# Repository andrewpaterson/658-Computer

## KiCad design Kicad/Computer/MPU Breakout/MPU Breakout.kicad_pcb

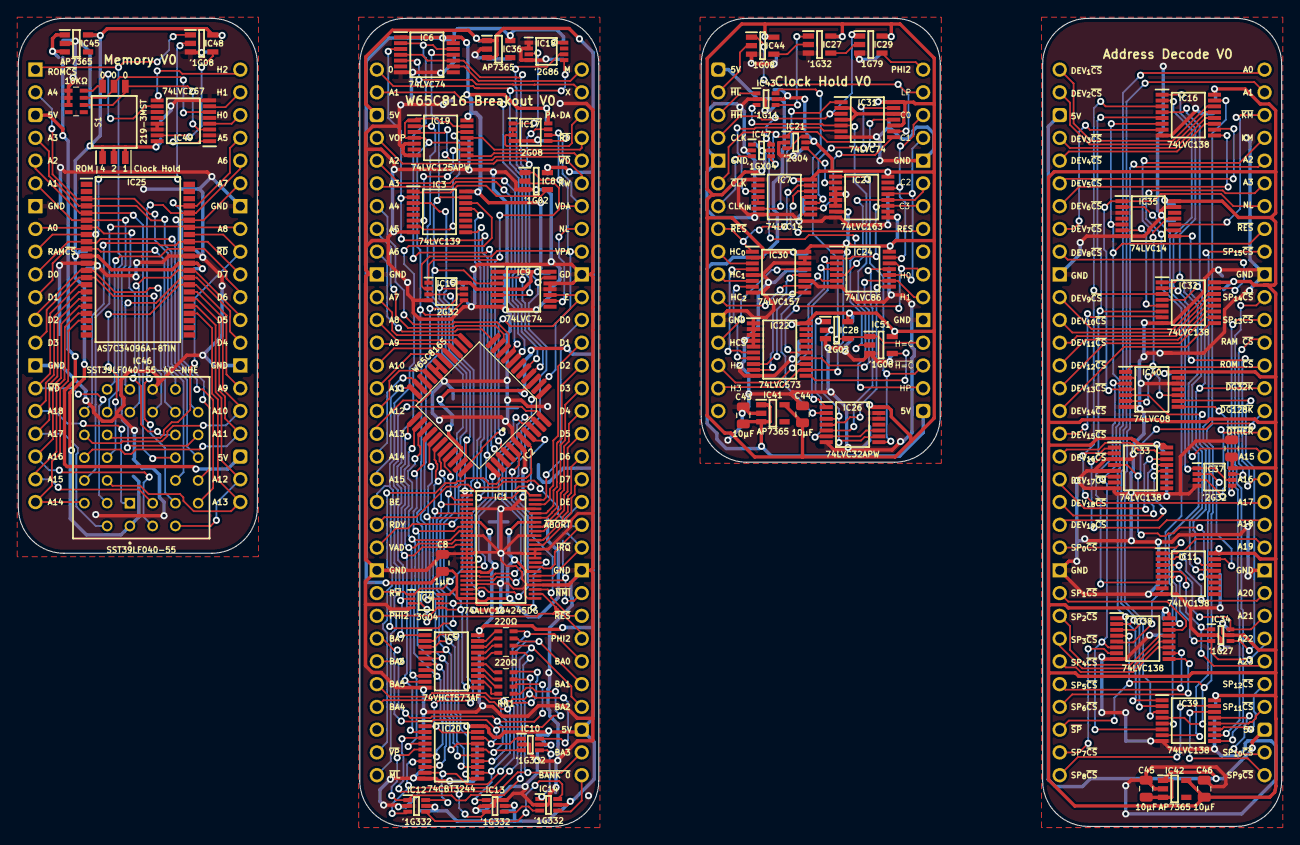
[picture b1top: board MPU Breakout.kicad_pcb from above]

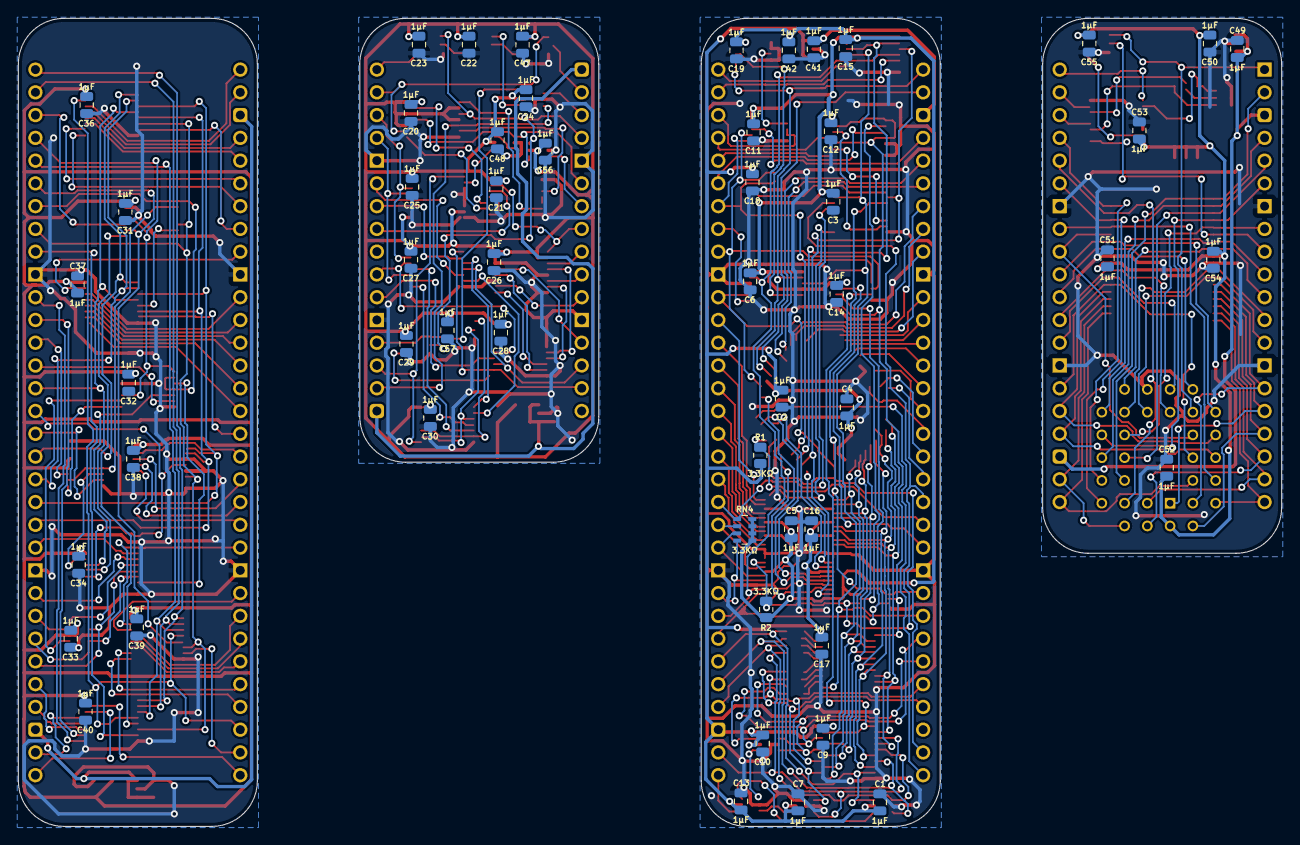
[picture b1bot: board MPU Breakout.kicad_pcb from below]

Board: 2 copper layers, 118 parts (54 on the bottom side), 254 nets.

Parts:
C1, C2, C3, C4, C5, C6, C7, C8, C9, C10, C11, C12, C13, C14, C15, C16, C17, C18, C19, C20, C21, C22, C23, C24, C25, C26, C27, C28, C29, C30, C31, C32, C33, C34, C35, C36, C37, C38, C39, C40, C41, C42, C47, C48, C49, C50, C51, C52, C53, C54, C55, C56, C57: 1μF; C_0805
C43, C44, C45, C46: 10μF; C_0805
IC1: 74ALVC164245DGG,11; SOP50P810X120-48N
IC2: W65C816S6TQG-14; W65C816 PLCC 0.8mm 44 Pin
IC3: 74LVC139PW,118; SOP65P640X110-16N
IC4: SN74LVC3G04DCUR; SOP50P310X90-8N
IC5: 74VHCT573AFT; SOP65P640X120-20N
IC6, IC9, IC31: 74LVC74APW,118; SOP65P640X110-14N
IC7, IC35: SN74LVC14APWRG4; SOP65P640X110-14N
IC8, IC28: 74LVC1G02GV,125; SOT95P275X110-5N
IC10, IC12, IC13, IC14: SN74LVC1G332DCKRG4; SOT65P210X110-6N
IC11, IC16, IC32, IC33, IC38, IC39: 74LVC138APW-Q100J; SOP65P640X110-16N
IC15, IC37: 74LVC2G32DP,125; SOP65P400X110-8N
IC17: 74LVC2G08DP-Q100H; SOP65P400X110-8N
IC18: 74LVC2G86DP,125; SOP65P400X110-8N
IC19: 74LVC125APW-Q100J; SOP65P640X110-14N
IC20: SN74CBT3244CPWR; SOP65P640X120-20N
IC21: 74LVC2G04GW-Q100H; SOP65P210X110-6N
IC22: 74LVC573APW,118; SOP65P640X110-20N
IC23: 74LVC163PW,118; SOP65P640X110-16N
IC24: SN74LVC86APWR; SOP65P640X120-14N
IC25: AS7C34096A-8TIN; SOP80P1176X120-44N
IC26: 74LVC32APW,118; SOP65P640X110-14N
IC27: 74LVC1G32GV,125; SOT95P275X110-5N
IC29: 74LVC1G79GV,125; SOT95P275X110-5N
IC30: 74LVC157APW,118; SOP65P640X110-16N
IC34: 74LVC1G27GW,125; SOP65P210X110-6N
IC36, IC41, IC42, IC45: AP7365-33WG-7; SOT95P285X130-5N
IC40: 74LVC08APW,112; SOP65P640X110-14N
IC43: 74LVC1G11GW-Q100H; SOP65P210X110-6N
IC44, IC48, IC51: 74LVC1G08GV,125; SOT95P275X110-5N
IC46: SST39LF040-55-4C-NHE; 5408803224008
IC47: 74LVC1GX04GW,125; SOP65P210X110-6N
IC49: 74LVC257APW,118; SOP65P640X110-16N
J1: Conn_02x16_Counter_Clockwise; DIP-32_Board_W22.86mm
J2, J7: Conn_02x32_Counter_Clockwise; DIP-64_Board_W22.86mm
J8: Conn_02x20_Counter_Clockwise; DIP-40_Board_W22.86mm
R1, R2: 3.3KΩ; R_0805
RN1, RN2: CAY16-221J4LF; CAY1647R0F4LF
RN3: CAY16-103J4LF; CAY16-J4
RN4: CAY16-332J4LF; CAY16332J4LF
S1: 219-3MST; SOIC127P844X265-6N

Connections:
/Address Decode Board/3.3V: C31.1, C32.1, C33.1, C34.1, C35.1, C36.1, C37.1, C38.1, C39.1, C40.1, C46.1, IC11.16 (3V), IC16.16 (3V), IC32.16 (3V), IC33.16 (3V), IC34.5 (3V), IC35.14 (3V), IC37.8 (VCC), IC38.16 (3V), IC39.16 (3V), IC40.14 (3V), IC42.5 (VOUT)
/Address Decode Board/5V: C45.1, IC42.1 (VIN), IC42.3 (EN), J2.3, J2.35
/Address Decode Board/A0: IC38.1 (A0), IC39.1 (A0), J2.64
/Address Decode Board/A1: IC38.2 (A1), IC39.2 (A1), J2.63
/Address Decode Board/A2: IC38.3 (A2), IC39.3 (A2), J2.60
/Address Decode Board/A3: IC35.9 (4A), IC38.5 (~E2), J2.59
/Address Decode Board/A15: IC16.1 (A0), IC32.1 (A0), J2.47
/Address Decode Board/A16: IC16.2 (A1), IC32.2 (A1), J2.46
/Address Decode Board/A17: IC16.3 (A2), IC32.3 (A2), IC33.1 (A0), J2.45
/Address Decode Board/A18: IC16.5 (~E2), IC32.6 (E3), IC33.2 (A1), J2.44
/Address Decode Board/A19: IC11.1 (A0), J2.43
/Address Decode Board/A20: IC11.2 (A1), J2.41
/Address Decode Board/A21: IC11.3 (A2), IC34.6 (C), J2.40
/Address Decode Board/A22: IC11.5 (~E2), IC34.3 (B), J2.39
/Address Decode Board/A23: IC11.4 (~E1), IC34.1 (A), J2.38
/Address Decode Board/GND: C31.2, C32.2, C33.2, C34.2, C35.2, C36.2, C37.2, C38.2, C39.2, C40.2, C45.2, C46.2, IC11.8 (GND), IC16.8 (GND), IC32.8 (GND), IC33.3 (A2), IC33.5 (~E2), IC33.8 (GND), IC34.2 (GND), IC35.3 (2A), IC35.7 (GND), IC35.13 (6A), IC37.4 (GND), IC38.8 (GND), IC39.8 (GND), IC40.7 (GND), IC40.12 (4A), IC40.13 (4B), IC42.2 (GND), J2.10, J2.23, J2.42, J2.55
/Address Decode Board/Kernal Mode: IC35.11 (5A), IC40.1 (1A), IC40.10 (3B), J2.61
/Address Decode Board/Kernal Mode·Native Latch: IC11.6 (E3), IC40.3 (1Y)
/Address Decode Board/Native Latch: IC35.1 (1A), IC40.2 (1B), IC40.4 (2A), J2.58
/Address Decode Board/~A21+A22+A23: IC34.4 (Y), IC40.9 (3A)
/Address Decode Board/~Device Group 32K: IC11.13 (~Y2), IC16.4 (~E1), IC32.4 (~E1), J2.50
/Address Decode Board/~Device Group 128K: IC11.12 (~Y3), IC33.4 (~E1), J2.49
/Address Decode Board/~Device _{CS1}: IC16.14 (~Y1), J2.1
/Address Decode Board/~Device _{CS2}: IC16.13 (~Y2), J2.2
/Address Decode Board/~Device _{CS3}: IC16.12 (~Y3), J2.4
/Address Decode Board/~Device _{CS4}: IC16.11 (~Y4), J2.5
/Address Decode Board/~Device _{CS5}: IC16.10 (~Y5), J2.6
/Address Decode Board/~Device _{CS6}: IC16.9 (~Y6), J2.7
/Address Decode Board/~Device _{CS7}: IC16.7 (~Y7), J2.8
/Address Decode Board/~Device _{CS8}: IC32.15 (~Y0), J2.9
/Address Decode Board/~Device _{CS9}: IC32.14 (~Y1), J2.11
/Address Decode Board/~Device _{CS10}: IC32.13 (~Y2), J2.12
/Address Decode Board/~Device _{CS11}: IC32.12 (~Y3), J2.13
/Address Decode Board/~Device _{CS12}: IC32.11 (~Y4), J2.14
/Address Decode Board/~Device _{CS13}: IC32.10 (~Y5), J2.15
/Address Decode Board/~Device _{CS14}: IC32.9 (~Y6), J2.16
/Address Decode Board/~Device _{CS15}: IC32.7 (~Y7), J2.17
/Address Decode Board/~Device _{CS16}: IC33.15 (~Y0), J2.18
/Address Decode Board/~Device _{CS17}: IC33.14 (~Y1), J2.19
/Address Decode Board/~Device _{CS18}: IC33.13 (~Y2), J2.20
/Address Decode Board/~Device _{CS19}: IC33.12 (~Y3), J2.21
/Address Decode Board/~Kernal Mode: IC35.10 (5Y), J2.62
/Address Decode Board/~Native Latch: IC35.2 (1Y), IC37.1 (1A), IC37.6 (2B)
/Address Decode Board/~OTHER: IC37.3 (2Y), J2.48
/Address Decode Board/~RAM_{CS}: IC37.7 (1Y), J2.52
/Address Decode Board/~ROM_{CS}: IC40.6 (2Y), J2.51
/Address Decode Board/~Reset: IC16.6 (E3), IC33.6 (E3), IC35.5 (3A), IC38.6 (E3), IC39.6 (E3), J2.57
/Address Decode Board/~SPECIAL: IC16.15 (~Y0), IC38.4 (~E1), IC39.4 (~E1), J2.30
/Address Decode Board/~Special _{CS0}: IC38.15 (~Y0), J2.22
/Address Decode Board/~Special _{CS1}: IC38.14 (~Y1), J2.24
/Address Decode Board/~Special _{CS2}: IC38.13 (~Y2), J2.25
/Address Decode Board/~Special _{CS3}: IC38.12 (~Y3), J2.26
/Address Decode Board/~Special _{CS4}: IC38.11 (~Y4), J2.27
/Address Decode Board/~Special _{CS5}: IC38.10 (~Y5), J2.28
/Address Decode Board/~Special _{CS6}: IC38.9 (~Y6), J2.29
/Address Decode Board/~Special _{CS7}: IC38.7 (~Y7), J2.31
/Address Decode Board/~Special _{CS8}: IC39.15 (~Y0), J2.32
/Address Decode Board/~Special _{CS9}: IC39.14 (~Y1), J2.33
/Address Decode Board/~Special _{CS10}: IC39.13 (~Y2), J2.34
/Address Decode Board/~Special _{CS11}: IC39.12 (~Y3), J2.36
/Address Decode Board/~Special _{CS12}: IC39.11 (~Y4), J2.37
/Address Decode Board/~Special _{CS13}: IC39.10 (~Y5), J2.53
/Address Decode Board/~Special _{CS14}: IC39.9 (~Y6), J2.54
/Address Decode Board/~Special _{CS15}: IC39.7 (~Y7), J2.56
/Clock Control Board/3.3V: C20.1, C21.1, C22.1, C23.1, C24.1, C25.1, C26.1, C27.1, C28.1, C29.1, C30.1, C44.1, C47.1, C48.1, C56.1, C57.1, IC7.14 (3V), IC21.5 (3V), IC22.20 (3V), IC23.7 (CEP), IC23.9 (~PE), IC23.10 (CET), IC23.16 (3V), IC24.14 (3V), IC26.14 (3V), IC27.5 (3V), IC28.5 (3V), IC29.5 (3V), IC30.2 (1I0), IC30.16 (3V), IC31.2 (1D), IC31.4 (~1SD), IC31.10 (~2SD), IC31.12 (2D), IC31.14 (3V), IC41.5 (VOUT), IC43.5 (3V), IC44.5 (3V), IC47.5 (3V), IC51.5 (3V)
/Clock Control Board/5V: C43.1, IC41.1 (VIN), IC41.3 (EN), J1.1, J1.17
/Clock Control Board/CLK: IC29.1 (D), IC31.3 (1CP), IC47.6 (Y), IC51.2 (A), J1.4
/Clock Control Board/CLK H.P.: IC7.4 (2Y), IC7.5 (3A)
/Clock Control Board/CLK High Pulse: IC31.5 (1Q), IC43.3 (B), J1.18
/Clock Control Board/CLK L.P.: IC7.8 (4Y), IC7.11 (5A)
/Clock Control Board/CLK Low Pulse: IC31.9 (2Q), IC44.1 (B), J1.31
/Clock Control Board/CLK_{IN}: IC47.3 (X1), J1.7
/Clock Control Board/Clk Count_{0}: IC23.14 (Q0), IC24.13 (4B), J1.30
/Clock Control Board/Clk Count_{1}: IC23.13 (Q1), IC24.10 (3B), J1.29
/Clock Control Board/Clk Count_{2}: IC23.12 (Q2), IC24.5 (2B), J1.27
/Clock Control Board/Clk Count_{3}: IC23.11 (Q3), IC24.2 (1B), J1.26
/Clock Control Board/GND: C20.2, C21.2, C22.2, C23.2, C24.2, C25.2, C26.2, C27.2, C28.2, C29.2, C30.2, C43.2, C44.2, C47.2, C48.2, C56.2, C57.2, IC7.1 (1A), IC7.7 (GND), IC21.2 (GND), IC22.1 (~OE), IC22.2 (D0), IC22.3 (D1), IC22.4 (D2), IC22.5 (D3), IC22.10 (GND), IC23.3 (D0), IC23.4 (D1), IC23.5 (D2), IC23.6 (D3), IC23.8 (GND), IC24.7 (GND), IC26.7 (GND), IC26.12 (4A), IC26.13 (4B), IC27.3 (GND), IC28.3 (GND), IC29.3 (GND), IC30.5 (2I0), IC30.8 (GND), IC30.11 (3I0), IC30.14 (4I0), IC30.15 (~E), IC31.7 (GND), IC41.2 (GND), IC43.2 (GND), IC44.3 (GND), IC47.2 (GND), IC51.3 (GND), J1.5, J1.12, J1.21, J1.28
/Clock Control Board/HC Latch_{0}: IC22.15 (Q4), IC24.12 (4A), J1.23
/Clock Control Board/HC Latch_{1}: IC22.14 (Q5), IC24.9 (3A), J1.22
/Clock Control Board/HC Latch_{2}: IC22.13 (Q6), IC24.4 (2A), J1.14
/Clock Control Board/HC Latch_{3}: IC22.12 (Q7), IC24.1 (1A), J1.15
/Clock Control Board/HC=CC: IC28.4 (Y), IC43.6 (C), IC51.1 (B), J1.20
/Clock Control Board/High Pulse+Low Pulse: IC27.4 (Y), IC29.2 (CP)
/Clock Control Board/Hold Count_{0}: IC22.6 (D4), IC30.4 (1Y)
/Clock Control Board/Hold Count_{0}D: IC30.3 (1I1), J1.9
/Clock Control Board/Hold Count_{1}: IC22.7 (D5), IC30.7 (2Y)
/Clock Control Board/Hold Count_{1}D: IC30.6 (2I1), J1.10
/Clock Control Board/Hold Count_{2}: IC22.8 (D6), IC30.9 (3Y)
/Clock Control Board/Hold Count_{2}D: IC30.10 (3I1), J1.11
/Clock Control Board/Hold Count_{3}: IC22.9 (D7), IC30.12 (4Y)
/Clock Control Board/Hold Count_{3}D: IC30.13 (4I1), J1.13
/Clock Control Board/Latch CHC: IC22.11 (LE), IC51.4 (Y)
/Clock Control Board/PHI2: IC29.4 (Q), J1.32
/Clock Control Board/Reset: IC7.12 (6Y), J1.25
/Clock Control Board/~CLK High Pulse: IC7.3 (2A), IC31.6 (~1Q)
/Clock Control Board/~CLK High Reset Pulse: IC7.6 (3Y), IC31.1 (~1RD)
/Clock Control Board/~CLK Low Pulse: IC7.9 (4A), IC31.8 (~2Q)
/Clock Control Board/~CLK Low Reset Pulse: IC7.10 (5Y), IC31.13 (~2RD)
/Clock Control Board/~CLK: IC21.1 (1A), IC31.11 (2CP), IC47.4 (~Y), J1.6
/Clock Control Board/~CLK_{DRAGGED}: IC21.4 (2Y), IC23.2 (CP)
/Clock Control Board/~HC=CC: IC23.1 (~MR), IC26.8 (3Y), J1.19
/Clock Control Board/~HC_{0=CC_{0}}: IC24.11 (4Y), IC26.5 (2B)
/Clock Control Board/~HC_{1=CC_{1}}: IC24.8 (3Y), IC26.4 (2A)
/Clock Control Board/~HC_{2=CC_{2}}: IC24.6 (2Y), IC26.2 (1B)
/Clock Control Board/~HC_{3=CC_{3}}: IC24.3 (1Y), IC26.1 (1A)
/Clock Control Board/~HC_{H=CC_{H}}: IC26.3 (1Y), IC26.9 (3A), IC28.2 (A)
/Clock Control Board/~HC_{L=CC_{L}}: IC26.6 (2Y), IC26.10 (3B), IC28.1 (B)
/Clock Control Board/~Hold High: IC43.1 (A), J1.3
/Clock Control Board/~Hold High·CLK High Pulse·HC=CC: IC27.1 (B), IC43.4 (Y)
/Clock Control Board/~Hold Low: IC44.2 (A), J1.2
/Clock Control Board/~Hold Low·CLK Low Pulse: IC27.2 (A), IC44.4 (Y)
/Clock Control Board/~Reset: IC7.13 (6A), IC30.1 (S), J1.8
/Memory Board/3.3V: C50.1, C51.1, C52.1, C53.1, C54.1, C55.1, IC25.11 (3V), IC25.33 (3V), IC45.5 (VOUT), IC46.32 (3V), IC48.5 (3V), IC49.16 (3V), S1.1, S1.2, S1.3
/Memory Board/5V: C49.1, IC45.1 (VIN), IC45.3 (EN), J8.3, J8.23
/Memory Board/A0: IC25.7 (A0), IC46.12 (A0), J8.8
/Memory Board/A1: IC25.6 (A1), IC46.11 (A1), J8.6
/Memory Board/A2: IC25.5 (A2), IC46.10 (A2), J8.5
/Memory Board/A3: IC25.4 (A3), IC46.9 (A3), J8.4
/Memory Board/A4: IC25.3 (A4), IC46.8 (A4), J8.2
/Memory Board/A5: IC25.41 (A5), IC46.7 (A5), J8.37
/Memory Board/A6: IC25.40 (A6), IC46.6 (A6), J8.36
/Memory Board/A7: IC25.39 (A7), IC46.5 (A7), J8.35
/Memory Board/A8: IC25.38 (A8), IC46.27 (A8), J8.33
/Memory Board/A9: IC25.30 (A9), IC46.26 (A9), J8.26
/Memory Board/A10: IC25.29 (A10), IC46.23 (A10), J8.25
/Memory Board/A11: IC25.28 (A11), IC46.25 (A11), J8.24
/Memory Board/A12: IC25.27 (A12), IC46.4 (A12), J8.22
/Memory Board/A13: IC25.26 (A13), IC46.28 (A13), J8.21
/Memory Board/A14: IC25.20 (A14), IC46.29 (A14), J8.20
/Memory Board/A15: IC25.19 (A15), IC46.3 (A15), J8.19
/Memory Board/A16: IC25.18 (A16), IC46.2 (A16), J8.18
/Memory Board/A17: IC25.17 (A17), IC46.30 (A17), J8.17
/Memory Board/A18: IC25.16 (A18), IC46.1 (A18), J8.16
/Memory Board/CH0_{OUT}: IC49.4 (1Y), J8.38
/Memory Board/CH1_{OUT}: IC49.7 (2Y), J8.39
/Memory Board/CH2_{OUT}: IC49.9 (3Y), J8.40
/Memory Board/D0: IC25.9 (DQ0), IC46.13 (DQ0), J8.10
/Memory Board/D1: IC25.10 (DQ1), IC46.14 (DQ1), J8.11
/Memory Board/D2: IC25.13 (DQ2), IC46.15 (DQ2), J8.12
/Memory Board/D3: IC25.14 (DQ3), IC46.17 (DQ3), J8.13
/Memory Board/D4: IC25.31 (DQ4), IC46.18 (DQ4), J8.28
/Memory Board/D5: IC25.32 (DQ5), IC46.19 (DQ5), J8.29
/Memory Board/D6: IC25.35 (DQ6), IC46.20 (DQ6), J8.30
/Memory Board/D7: IC25.36 (DQ7), IC46.21 (DQ7), J8.31
/Memory Board/GND: C49.2, C50.2, C51.2, C52.2, C53.2, C54.2, C55.2, IC25.12 (GND), IC25.34 (GND), IC45.2 (GND), IC46.16 (GND), IC48.3 (GND), IC49.2 (1I0), IC49.5 (2I0), IC49.8 (GND), IC49.11 (3I0), IC49.13 (4I1), IC49.14 (4I0), J8.7, J8.14, J8.27, J8.34, RN3.1 (R1), RN3.2 (R2), RN3.3 (R3)
/Memory Board/SW_{0}: IC49.3 (1I1), RN3.6 (R3), S1.4
/Memory Board/SW_{1}: IC49.6 (2I1), RN3.7 (R2), S1.5
/Memory Board/SW_{2}: IC49.10 (3I1), RN3.8 (R1), S1.6
/Memory Board/~RAM_{CS}: IC25.8 (~CE), IC48.2 (A), IC49.1 (S), J8.9
/Memory Board/~RAM_{CS}·~ROM_{CS}: IC48.4 (Y), IC49.15 (~OE)
/Memory Board/~RD: IC25.37 (~OE), IC46.24 (~OE), J8.32
/Memory Board/~ROM_{CS}: IC46.22 (~CE), IC48.1 (B), J8.1
/Memory Board/~WD: IC25.15 (~WE), IC46.31 (~WE), J8.15
/W65C816 Breakout Board/3.3V: C3.1, C5.1, C6.1, C8.1, C11.1, C12.1, C14.1, C15.1, C19.1, C42.1, IC1.24 (2DIR), IC1.31 (3V), IC1.42 (3V), IC3.16 (3V), IC4.8 (3V), IC6.1 (~1RD), IC6.13 (~2RD), IC6.14 (3V), IC9.1 (~1RD), IC9.4 (~1SD), IC9.14 (3V), IC15.8 (VCC), IC17.8 (3V), IC18.8 (VCC), IC19.14 (3V), IC36.5 (VOUT), R2.2, RN4.1 (R1), RN4.2 (R2), RN4.3 (R3), RN4.4 (R4)
/W65C816 Breakout Board/5V: C1.1, C2.1, C4.1, C7.1, C9.1, C10.1, C13.1, C16.1, C17.1, C18.1, C41.1, IC1.7 (5V), IC1.18 (5V), IC2.9 (VCC), IC2.37 (VCC), IC5.20 (5V), IC8.5 (3V), IC10.5 (3V), IC12.5 (3V), IC13.5 (3V), IC14.5 (3V), IC20.20 (5V), IC36.1 (VIN), IC36.3 (EN), J7.3, J7.35, R1.1
/W65C816 Breakout Board/A0: IC2.10 (A0), IC9.2 (1D), IC18.5 (2A), J7.1
/W65C816 Breakout Board/A0_{CHANGE}: IC17.1 (1A), IC18.3 (2Y)
/W65C816 Breakout Board/A0_{PREV}: IC9.5 (1Q), IC18.6 (2B)
/W65C816 Breakout Board/A1: IC2.11 (A1), J7.2
/W65C816 Breakout Board/A2: IC2.13 (A2), J7.5
/W65C816 Breakout Board/A3: IC2.14 (A3), J7.6
/W65C816 Breakout Board/A4: IC2.15 (A4), J7.7
/W65C816 Breakout Board/A5: IC2.16 (A5), J7.8
/W65C816 Breakout Board/A6: IC2.17 (A6), J7.9
/W65C816 Breakout Board/A7: IC2.18 (A7), J7.11
/W65C816 Breakout Board/A8: IC2.19 (A8), J7.12
/W65C816 Breakout Board/A9: IC2.20 (A9), J7.13
/W65C816 Breakout Board/A10: IC2.21 (A10), J7.14
/W65C816 Breakout Board/A11: IC2.22 (A11), J7.15
/W65C816 Breakout Board/A12: IC2.25 (A12), J7.16
/W65C816 Breakout Board/A13: IC2.26 (A13), J7.17
/W65C816 Breakout Board/A14: IC2.27 (A14), J7.18
/W65C816 Breakout Board/A15: IC2.28 (A15), J7.19
/W65C816 Breakout Board/Address Valid: IC15.7 (1Y), J7.22
/W65C816 Breakout Board/BA0: IC12.6 (C), IC20.9 (2B1), J7.38, RN2.8 (R1)
/W65C816 Breakout Board/BA0+BA1+BA2: IC12.4 (Y), IC14.6 (C)
/W65C816 Breakout Board/BA1: IC12.3 (B), IC20.7 (2B2), J7.37, RN2.7 (R2)
/W65C816 Breakout Board/BA2: IC12.1 (A), IC20.5 (2B3), J7.36, RN2.6 (R3)
/W65C816 Breakout Board/BA3: IC13.3 (B), IC20.3 (2B4), J7.34, RN2.5 (R4)
/W65C816 Breakout Board/BA3+BA4: IC13.4 (Y), IC14.3 (B)
/W65C816 Breakout Board/BA4: IC13.1 (A), IC20.12 (1B4), J7.29, RN1.8 (R1)
/W65C816 Breakout Board/BA5: IC10.6 (C), IC20.14 (1B3), J7.28, RN1.7 (R2)
/W65C816 Breakout Board/BA5+BA6+BA7: IC10.4 (Y), IC14.1 (A)
/W65C816 Breakout Board/BA6: IC10.3 (B), IC20.16 (1B2), J7.27, RN1.6 (R3)
/W65C816 Breakout Board/BA7: IC10.1 (A), IC20.18 (1B1), J7.26, RN1.5 (R4)
/W65C816 Breakout Board/BE: IC1.33 (2A2), IC3.14 (2A0), IC4.6 (3A), J7.20, R2.1
/W65C816 Breakout Board/BE_{5V}: IC1.16 (2B2), IC2.40 (BE)
/W65C816 Breakout Board/D0: IC1.47 (1A0), J7.53
/W65C816 Breakout Board/D0_{65}: IC1.2 (1B0), IC2.36 (D0), IC5.2 (D0), IC20.11 (2A1)
/W65C816 Breakout Board/D0_{VHC}: IC5.19 (Q0), RN2.1 (R1)
/W65C816 Breakout Board/D1: IC1.46 (1A1), J7.52
/W65C816 Breakout Board/D1_{65}: IC1.3 (1B1), IC2.35 (D1), IC5.3 (D1), IC20.13 (2A2)
/W65C816 Breakout Board/D1_{VHC}: IC5.18 (Q1), RN2.2 (R2)
/W65C816 Breakout Board/D2: IC1.44 (1A2), J7.51
/W65C816 Breakout Board/D2_{65}: IC1.5 (1B2), IC2.34 (D2), IC5.4 (D2), IC20.15 (2A3)
/W65C816 Breakout Board/D2_{VHC}: IC5.17 (Q2), RN2.3 (R3)
/W65C816 Breakout Board/D3: IC1.43 (1A3), J7.50
/W65C816 Breakout Board/D3_{65}: IC1.6 (1B3), IC2.33 (D3), IC5.5 (D3), IC20.17 (2A4)
/W65C816 Breakout Board/D3_{VHC}: IC5.16 (Q3), RN2.4 (R4)
/W65C816 Breakout Board/D4: IC1.41 (1A4), J7.49
/W65C816 Breakout Board/D4_{65}: IC1.8 (1B4), IC2.32 (D4), IC5.6 (D4), IC20.8 (1A4)
/W65C816 Breakout Board/D4_{VHC}: IC5.15 (Q4), RN1.1 (R1)
/W65C816 Breakout Board/D5: IC1.40 (1A5), J7.48
/W65C816 Breakout Board/D5_{65}: IC1.9 (1B5), IC2.31 (D5), IC5.7 (D5), IC20.6 (1A3)
/W65C816 Breakout Board/D5_{VHC}: IC5.14 (Q5), RN1.2 (R2)
/W65C816 Breakout Board/D6: IC1.38 (1A6), J7.47
/W65C816 Breakout Board/D6_{65}: IC1.11 (1B6), IC2.30 (D6), IC5.8 (D6), IC20.4 (1A2)
/W65C816 Breakout Board/D6_{VHC}: IC5.13 (Q6), RN1.3 (R3)
/W65C816 Breakout Board/D7: IC1.37 (1A7), J7.46
/W65C816 Breakout Board/D7_{65}: IC1.12 (1B7), IC2.29 (D7), IC5.9 (D7), IC20.2 (1A1)
/W65C816 Breakout Board/D7_{VHC}: IC5.12 (Q7), RN1.4 (R4)
/W65C816 Breakout Board/DE: IC3.13 (2A1), J7.45, RN4.5 (R4)
/W65C816 Breakout Board/E: IC2.39 (E), IC9.10 (~2SD), J7.54
/W65C816 Breakout Board/FET ~OE: IC15.3 (2Y), IC20.1 (1~OE), IC20.19 (2~OE)
/W65C816 Breakout Board/GND: C1.2, C2.2, C3.2, C4.2, C5.2, C6.2, C7.2, C8.2, C9.2, C10.2, C11.2, C12.2, C13.2, C14.2, C15.2, C16.2, C17.2, C18.2, C19.2, C41.2, C42.2, IC1.4 (GND), IC1.10 (GND), IC1.13 (2B0), IC1.14 (2B1), IC1.15 (GND), IC1.21 (GND), IC1.25 (2~OE), IC1.28 (GND), IC1.34 (GND), IC1.35 (2A1), IC1.36 (2A0), IC1.39 (GND), IC1.45 (GND), IC2.1 (GND), IC2.23 (GND), IC2.24 (GND), IC3.8 (GND), IC4.4 (GND), IC5.10 (GND), IC6.7 (GND), IC8.3 (GND), IC9.7 (GND), IC9.11 (2CP), IC9.12 (2D), IC10.2 (GND), IC12.2 (GND), IC13.2 (GND), IC13.6 (C), IC14.2 (GND), IC15.4 (GND), IC17.4 (GND), IC18.1 (1A), IC18.2 (1B), IC18.4 (GND), IC19.5 (2A), IC19.7 (GND), IC20.10 (GND), IC36.2 (GND), J7.10, J7.23, J7.42, J7.55
/W65C816 Breakout Board/M: IC6.9 (2Q), J7.64
/W65C816 Breakout Board/MX: IC2.42 (MX), IC6.2 (1D), IC6.12 (2D)
/W65C816 Breakout Board/Native Latch: IC9.9 (2Q), J7.57
/W65C816 Breakout Board/Opcode Valid: IC17.7 (1Y), J7.4
/W65C816 Breakout Board/PHI2: IC1.26 (2A7), IC4.3 (2A), IC15.6 (2B), J7.39
/W65C816 Breakout Board/PHI2_{5V}: IC1.23 (2B7), IC2.41 (PHI2), IC3.2 (1A0), IC6.3 (1CP)
/W65C816 Breakout Board/RDY: IC2.3 (RDY), J7.21, R1.2
/W65C816 Breakout Board/RW_{PART}: IC4.7 (1Y), IC19.2 (1A)
/W65C816 Breakout Board/R~W: IC1.1 (1DIR), IC2.38 (R~W), IC3.3 (1A1), IC4.1 (1A), J7.24
/W65C816 Breakout Board/VDA: IC2.43 (VDA), IC8.2 (A), IC15.1 (1A), IC17.5 (2A), J7.58
/W65C816 Breakout Board/VPA: IC2.8 (VPA), IC8.1 (B), IC15.2 (1B), IC17.6 (2B), J7.56
/W65C816 Breakout Board/VPA·VDA: IC17.2 (1B), IC17.3 (2Y), J7.62
/W65C816 Breakout Board/X: IC6.5 (1Q), J7.63
/W65C816 Breakout Board/~ABORT: IC1.32 (2A3), J7.44, RN4.6 (R3)
/W65C816 Breakout Board/~ABORT_{5V}: IC1.17 (2B3), IC2.4 (~ABORT)
/W65C816 Breakout Board/~BANK 0: IC14.4 (Y), J7.33
/W65C816 Breakout Board/~BE: IC4.2 (3Y), IC5.1 (~OE), IC15.5 (2A), IC19.1 (~1OE), IC19.4 (~2OE), IC19.10 (~3OE), IC19.13 (~4OE)
/W65C816 Breakout Board/~DE: IC1.48 (1~OE), IC3.9 (~2Y3)
/W65C816 Breakout Board/~IRQ: IC1.30 (2A4), J7.43, RN4.7 (R2)
/W65C816 Breakout Board/~IRQ_{5V}: IC1.19 (2B4), IC2.5 (~IRQ)
/W65C816 Breakout Board/~ML: IC2.6 (~ML), J7.32
/W65C816 Breakout Board/~NMI: IC1.29 (2A5), J7.41, RN4.8 (R1)
/W65C816 Breakout Board/~NMI_{5V}: IC1.20 (2B5), IC2.7 (~NMI)
/W65C816 Breakout Board/~PHI2: IC3.15 (~2E), IC4.5 (2Y), IC5.11 (LE), IC6.11 (2CP), IC9.3 (1CP), J7.25
/W65C816 Breakout Board/~RD: IC19.11 (4Y), J7.61
/W65C816 Breakout Board/~RD_{PART}: IC3.7 (~1Y3), IC19.12 (4A)
/W65C816 Breakout Board/~RES_{5V}: IC1.22 (2B6), IC2.44 (~RES)
/W65C816 Breakout Board/~Reset: IC1.27 (2A6), IC6.4 (~1SD), IC6.10 (~2SD), IC9.13 (~2RD), J7.40
/W65C816 Breakout Board/~RW: IC19.3 (1Y), J7.59
/W65C816 Breakout Board/~VPA+VDA: IC3.1 (~1E), IC8.4 (Y)
/W65C816 Breakout Board/~VP: IC2.2 (~VP), J7.31
/W65C816 Breakout Board/~WD: IC19.8 (3Y), J7.60
/W65C816 Breakout Board/~WD_{PART}: IC3.6 (~1Y2), IC19.9 (3A)
unnamed: IC11.15 (~Y0), IC37.2 (1B)
unnamed: IC11.14 (~Y1), IC40.5 (2B)
unnamed: IC21.3 (2A), IC21.6 (1Y)
unnamed: IC32.5 (~E2), IC35.6 (3Y)
unnamed: IC35.8 (4Y), IC39.5 (~E2)
unnamed: IC37.5 (2A), IC40.8 (3Y)
